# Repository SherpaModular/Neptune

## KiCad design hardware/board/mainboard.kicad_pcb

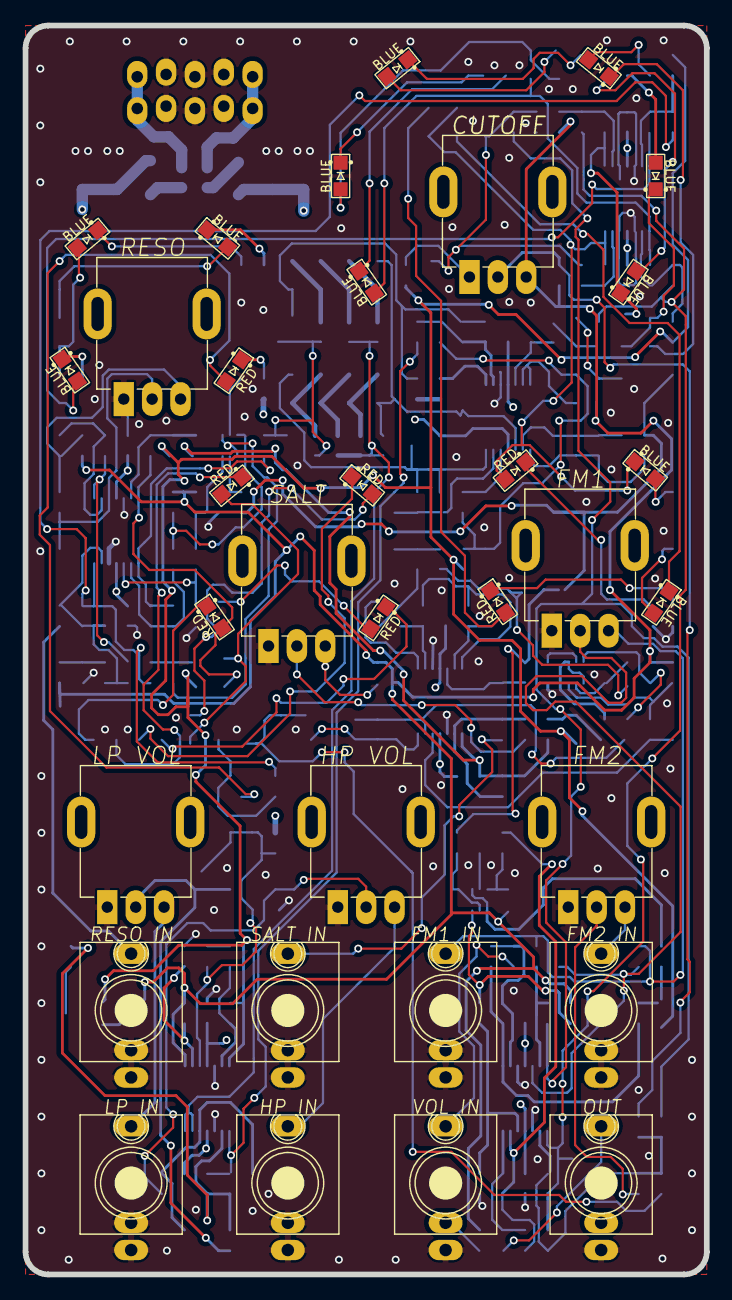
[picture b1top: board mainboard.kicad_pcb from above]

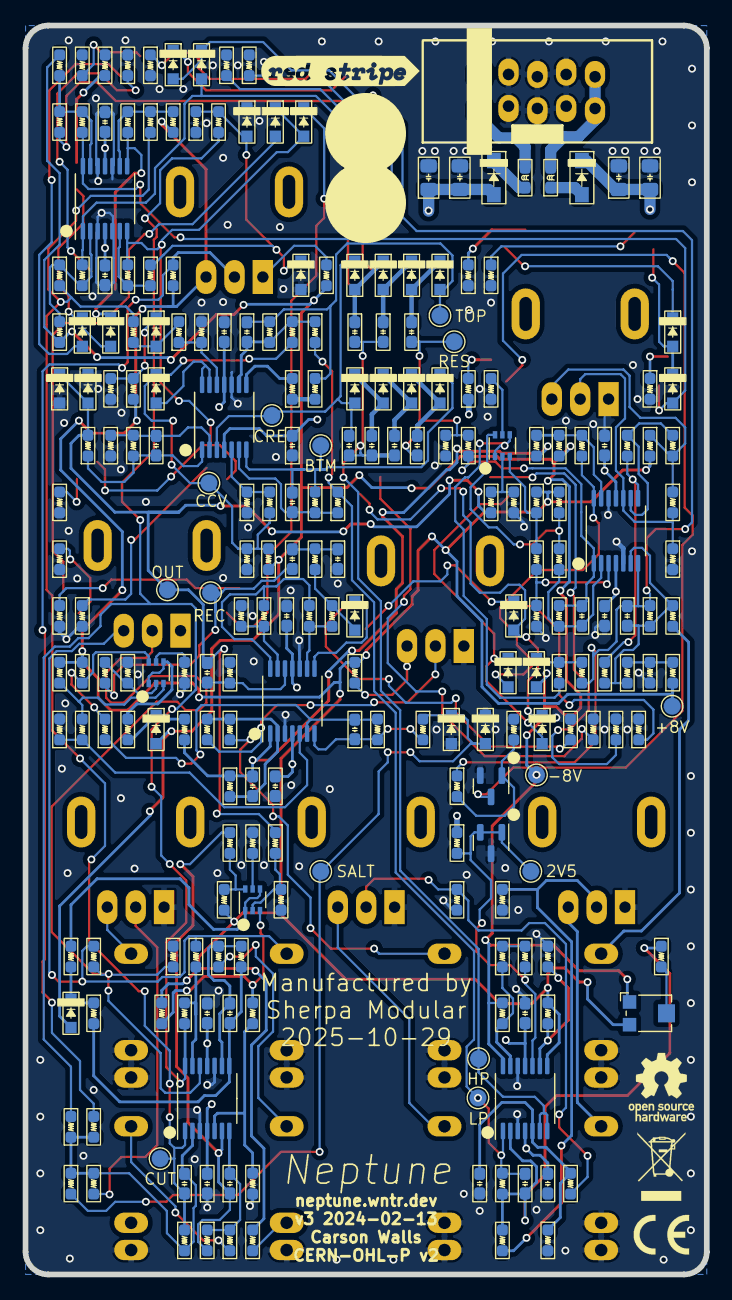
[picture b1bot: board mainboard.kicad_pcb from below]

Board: 4 copper layers, 60.0 x 110.0 mm, 273 parts (240 on the bottom side), 151 nets.

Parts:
C201, C202, C203, C204: 10u; C_0805_HandSolder
C206, C207, C208, C209, C210, C211, C212, C213, C214, C215, C216, C217: 100n; C_0603_HandSolder
C301, C302, C503, C504, C505, C506, C507, C508, C509: 1n; C_0603_HandSolder
C401, C501, C502, C510, C705: 100p; C_0603_HandSolder
C601, C702, C704, C801: 330p; C_0603_HandSolder
C602, C802: 10p; C_0603_HandSolder
C701, C703: 220n; C_0603_HandSolder
D201, D202: 30V; D_SOD-123+SOD-123F
D501, D502, D503, D504, D505, D506, D507, D508, D509, D510, D511, D512, D601, D701, D702, D703, D704, D801, D902, D904, D907, D909, D912, D914, D916, D919, D921, D927, D928, D929, D930: BAS315; D_SOD-323
D901, D903, D905, D906, D908, D910, D918, D920, D922, D925, D931: BLUE; LED_0805_Kingbright_APT2012
D911, D913, D915, D917, D924, D926, D932: RED; LED_0805_Kingbright_APT2012
FB201, FB202: 1k @ 100MHz; L_0603_HandSolder
J201: Power; Eurorack_Power_2x5_Shrouded_Lock_LongPads
J301, J302, J401, J402, J601, J701, J801, J802: AudioJack_WQP518MA_Compact_S_LongPads
Q601, Q701, Q801: BCM847; SOT-363_SC-70-6
Q901: MMBT3906; SOT-23
R201, R203, R303, R306, R515, R516, R519, R603, R604, R605, R612, R624, R704, R705, R713, R722, R804, R815, R904, R905, R906, R910, R911, R912, R916, R917, R918, R919, R923, R924, R925, R929, R930, R931, R932, R933, R935: 1k; R_0603_HandSolder
R202, R302, R305, R403, R404, R505, R606, R607, R609, R610, R611, R702, R710, R711, R712, R901, R907, R908: 100k; R_0603_HandSolder
R204, R405, R409, R518, R802, R803, R903, R909: 68k; R_0603_HandSolder
R205, R206, R307, R621, R622, R720, R721: 220k; R_0603_HandSolder
R301, R304, R501, R504, R602, R623, R709: 5k6; R_0603_HandSolder
R401, R410, R411, R517, R614, R619, R620, R718, R719: 3k9; R_0603_HandSolder
R402, R706, R707, R801, R915, R927: 39k; R_0603_HandSolder
R406, R407, R507, R913, R922: 33k; R_0603_HandSolder
R408, R601, R613, R701, R703, R714, R805, R806, R811, R812, R920: 10k; R_0603_HandSolder
R502, R926, R934, R936: 1k8; R_0603_HandSolder
R503, R608, R813, R814, R902, R914, R921, R928: 330k; R_0603_HandSolder
R506, R508, R509, R510, R511, R512, R513, R514, R617, R618, R716, R717, R809, R810: 20k; R_0603_HandSolder
R615, R616, R708, R715, R807, R808: 100R; R_0603_HandSolder
RV301, RV302, RV401, RV402, RV403, RV601, RV701: 10k; Potentiometer_Alpha_R0904N_LongPads
RV303: 10k; Potentiometer_Bourns_TC33X_Vertical
TP201, TP202, TP203, TP401, TP501, TP502, TP503, TP504, TP505, TP506, TP507, TP508, TP701, TP702: TestPoint_Pad_D1.5mm
U1, U2, U3, U4, U5, U6: TL074; TSSOP-14_4.4x5mm_P0.65mm
U201: TL431A; SOT-23

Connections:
+8VREF: R205.1, R402.1, R504.1, R601.1, R602.2, R617.2, R618.1, R709.2, R716.2, R717.1, R801.2, R809.2, R810.1, R908.2, RV303.3, RV401.3, TP202.1, U1.8
+12V: C201.1, C203.1, C206.2, C208.2, C210.2, C212.2, C214.2, C216.2, D201.1 (K), R201.1, U1.4 (V+), U2.4 (V+), U3.4 (V+), U4.4 (V+), U5.4 (V+), U6.4 (V+)
-8VREF: D601.2 (A), D702.2 (A), D801.2 (A), R206.1, R401.2, R506.2, R902.2, R914.2, R921.2, RV303.1, TP203.1, U1.14
-12V: C202.1, C204.1, C207.2, C209.2, C211.2, C213.2, C215.2, C217.2, D202.2 (A), R926.1, U1.11 (V-), U2.11 (V-), U3.11 (V-), U4.11 (V-), U5.11 (V-), U6.11 (V-)
/Cutoff CV Driver/CUTOFF_OUT: C401.1, R409.2, R501.2, R901.2, R907.2, TP401.1, U2.1
/Cutoff CV Driver/FM1_OUT: R404.1, R406.2, R933.1, U2.14
/Cutoff CV Driver/SALT_IN: D703.1 (K), D704.2 (A), R408.2, R722.1, TP702.1
/Filter Core/HIGH_PASS_IN: C504.2, C505.2, C506.2, C507.2, C508.2, TP504.1, U1.6 (-), U1.7
/Filter Core/LOW_PASS_IN: C301.1, R303.1, R509.2, R510.2, TP502.1, U1.1
/Filter Core/OUT: C701.2, D511.1 (K), D512.2 (A), R519.2, R614.2, R805.1, TP508.1
/Filter Core/RESONANCE_IN: C503.2, C509.2, R623.2, R624.1, TP503.1
/LED Drivers/RESONANCE_CV_IN: C601.1, R611.1, R612.2, R920.2, R935.1, U4.7
/LED Drivers/SALT_CV_IN: C704.1, R712.1, R713.2, R913.2, U5.1
/Power/2.5v unbuffered: R201.2, R203.1, TP201.1, U1.10 (+), U201.1 (K), U201.2 (REF)
/Resonance VCA/Resonance_CV: J601.T (Tip), R608.2
/Resonance VCA/Resonance_Offset: R601.2, R603.2, R609.2
/Resonance VCA/Resonance_Potentiometer: R607.1, R610.2, U4.8
GND: C201.2, C202.2, C203.2, C204.2, C206.1, C207.1, C208.1, C209.1, C210.1, C211.1, C212.1, C213.1, C214.1, C215.1, C216.1, C217.1, C302.2, C702.2, D511.2 (A), D512.1 (K), D703.2 (A), D704.1 (K), D929.1 (K), D930.2 (A), J201.3 (GND), J201.4 (GND), J201.5 (GND), J201.6 (GND), J201.7 (GND), J201.8 (GND), J301.S (Sleeve), J301.TN (Tip_normalize), J302.S (Sleeve), J302.TN (Tip_normalize), J401.S (Sleeve), J401.TN (Tip_normalize), J402.S (Sleeve), J402.TN (Tip_normalize), J601.S (Sleeve), J601.TN (Tip_normalize), J701.S (Sleeve), J701.TN (Tip_normalize), J801.S (Sleeve), J802.S (Sleeve), Q901.2 (E), R202.2, R301.2, R304.2, R306.2, R411.2, R502.2, R505.2, R507.1, R512.1, R517.1, R603.1, R605.2, R615.2, R616.1, R621.2, R624.2, R701.2, R702.1, R708.2, R715.1, R720.2, R807.2, R808.1, R813.2, R904.2, R905.2, R906.2, R910.2, R911.2, R912.2, R916.2, R917.2, R918.2, R919.2, R923.2, R924.2, R925.2, R929.1, R930.2, R931.1, R932.2, R934.1, R936.2, RV301.1, RV302.1, RV402.1, RV403.1, RV601.1, RV701.1, U1.3 (+), U1.12 (+), U2.3 (+), U2.10 (+), U3.10 (+), U4.5 (+), U4.12 (+), U5.3 (+), U5.10 (+), U6.3 (+), U6.5 (+), U6.10 (+), U6.12 (+), U201.3 (A)
unnamed: C510.1, R518.2, R519.1, U3.1
unnamed: C602.2, R622.1, R623.1, U4.1
unnamed: C702.1, C703.2, R706.1
unnamed: C703.1, R707.1, TP701.1
unnamed: C705.1, R721.1, R722.2, U5.7
unnamed: C801.1, R803.1, R804.2, U2.8
unnamed: C802.2, R814.1, R815.2, U2.7
unnamed: D201.2 (A), FB201.1
unnamed: D202.1 (K), FB202.1
unnamed: D501.2 (A), R501.1, R503.2
unnamed: D501.1 (K), R502.1, R504.2
unnamed: D502.2 (A), U3.13 (-), U3.14
unnamed: D502.1 (K), R506.1, R507.2, R508.2, R511.2, TP501.1
unnamed: C501.1, D503.2 (A), R513.1, R515.1, TP505.1
unnamed: C503.1, D503.1 (K), D504.2 (A)
unnamed: C504.1, D504.1 (K), D505.2 (A)
unnamed: C505.1, D505.1 (K), D506.2 (A)
unnamed: C506.1, D506.1 (K), D507.2 (A), TP507.1, U3.3 (+)
unnamed: C507.1, D507.1 (K), D508.2 (A)
unnamed: C508.1, D508.1 (K), D509.2 (A)
unnamed: C509.1, D509.1 (K), D510.2 (A)
unnamed: C502.1, D510.1 (K), R514.1, TP506.1, U3.7
unnamed: D601.1 (K), R612.1, R613.2
unnamed: D701.2 (A), R705.1, R706.2
unnamed: D701.1 (K), U5.8
unnamed: D702.1 (K), R713.1, R714.2
unnamed: D801.1 (K), R804.1, R806.2
unnamed: D901.2 (A), D902.2 (A), R903.2, U6.1
unnamed: D901.1 (K), R904.1
unnamed: D902.1 (K), D903.2 (A), D904.2 (A)
unnamed: D903.1 (K), R905.1
unnamed: D904.1 (K), D905.2 (A)
unnamed: D905.1 (K), R906.1
unnamed: D906.2 (A), R910.1
unnamed: D906.1 (K), D907.1 (K), R909.2, U6.8
unnamed: D907.2 (A), D908.1 (K), D909.1 (K)
unnamed: D908.2 (A), R911.1
unnamed: D909.2 (A), D910.1 (K)
unnamed: D910.2 (A), R912.1
unnamed: D911.2 (A), D912.2 (A), R915.2, U4.14
unnamed: D911.1 (K), R916.1
unnamed: D912.1 (K), D913.2 (A), D914.2 (A)
unnamed: D913.1 (K), R917.1
unnamed: D914.1 (K), D915.2 (A), D916.2 (A)
unnamed: D915.1 (K), R918.1
unnamed: D916.1 (K), D917.2 (A)
unnamed: D917.1 (K), R919.1
unnamed: D918.2 (A), D919.2 (A), R922.1, U6.14
unnamed: D918.1 (K), R923.1
unnamed: D919.1 (K), D920.2 (A), D921.2 (A)
unnamed: D920.1 (K), R924.1
unnamed: D921.1 (K), D922.2 (A)
unnamed: D922.1 (K), R925.1
unnamed: D924.2 (A), Q901.3 (C)
unnamed: D924.1 (K), R926.2
unnamed: D925.2 (A), R929.2
unnamed: D925.1 (K), D926.2 (A), D927.1 (K), D928.2 (A), R928.1, U6.7
unnamed: D926.1 (K), R930.1
unnamed: D927.2 (A), D931.1 (K)
unnamed: D928.1 (K), D932.2 (A)
unnamed: D929.2 (A), D930.1 (K), R927.1, R933.2, R934.2
unnamed: D931.2 (A), R931.2
unnamed: D932.1 (K), R932.1
unnamed: FB201.2, J201.9 (+12V), J201.10 (+12V)
unnamed: FB202.2, J201.1 (-12V), J201.2 (-12V)
unnamed: J301.T (Tip), RV301.3
unnamed: J302.T (Tip), RV302.3
unnamed: J401.T (Tip), R403.2, R410.1, RV402.3
unnamed: J402.T (Tip), RV403.3
unnamed: J701.T (Tip), R710.2
unnamed: J801.T (Tip), R802.2
unnamed: J801.TN (Tip_normalize), R801.1
unnamed: J802.T (Tip), R815.1
unnamed: Q601.2 (B), R614.1, R615.1
unnamed: Q601.5 (B), R616.2
unnamed: Q601.3 (C), R618.2, R620.2
unnamed: Q601.6 (C), R617.1, R619.2
unnamed: Q601.1 (E), Q601.4 (E), R613.1
unnamed: Q701.2 (B), R707.2, R708.1
unnamed: Q701.5 (B), R715.2
unnamed: Q701.3 (C), R717.2, R719.2
unnamed: Q701.6 (C), R716.1, R718.2
unnamed: Q701.1 (E), Q701.4 (E), R714.1
unnamed: Q801.2 (B), R805.2, R807.1
unnamed: Q801.5 (B), R808.2
unnamed: Q801.3 (C), R810.2, R812.2
unnamed: Q801.6 (C), R809.1, R811.2
unnamed: Q801.1 (E), Q801.4 (E), R806.1
unnamed: Q901.1 (B), R935.2, R936.1
unnamed: R203.2, R204.1
unnamed: R301.1, R302.2, RV301.2
unnamed: R304.1, R305.2, RV302.2
unnamed: R307.2, RV303.2
unnamed: R401.1, RV401.1
unnamed: R402.2, R405.1, RV401.2
unnamed: R407.2, RV403.2
unnamed: R515.2, R516.1
unnamed: R516.2, U3.8
unnamed: R602.1, R604.1, R606.2, RV601.3
unnamed: R703.1, R704.2, U5.14
unnamed: R709.1, RV701.3
unnamed: R711.2, RV701.2
unnamed: C301.2, R302.1, R303.2, R307.1, U1.2 (-)
unnamed: C302.1, R305.1, R306.1, U1.5 (+)
unnamed: R202.1, R205.2, U1.9 (-)
unnamed: R204.2, R206.2, U1.13 (-)
unnamed: C401.2, R405.2, R406.1, R407.1, R408.1, R409.1, U2.2 (-)
unnamed: R812.1, R813.1, U2.5 (+)
unnamed: C802.1, R811.1, R814.2, U2.6 (-)
unnamed: C801.2, R802.1, R803.2, U2.9 (-)
unnamed: R410.2, R411.1, RV402.2, U2.12 (+)
unnamed: R403.1, R404.2, U2.13 (-)
unnamed: C510.2, R517.2, R518.1, U3.2 (-)
unnamed: R511.1, R512.2, U3.5 (+)
unnamed: C502.2, R510.1, R514.2, U3.6 (-)
unnamed: C501.2, R508.1, R509.1, R513.2, U3.9 (-)
unnamed: R503.1, R505.1, U3.12 (+)
unnamed: R620.1, R621.1, U4.3 (+)
unnamed: C602.1, R619.1, R622.2, U4.2 (-)
unnamed: C601.2, R608.1, R609.1, R610.1, R611.2, U4.6 (-)
unnamed: R604.2, R605.1, RV601.2, U4.10 (+)
unnamed: R606.1, R607.2, U4.9 (-)
unnamed: R913.1, R914.1, R915.1, U4.13 (-)
unnamed: C704.2, R710.1, R711.1, R712.2, U5.2 (-)
unnamed: R719.1, R720.1, U5.5 (+)
unnamed: C705.2, R718.1, R721.2, U5.6 (-)
unnamed: R704.1, R705.2, U5.9 (-)
unnamed: C701.1, R702.2, U5.12 (+)
unnamed: R701.1, R703.2, U5.13 (-)
unnamed: R901.1, R902.1, R903.1, U6.2 (-)
unnamed: R927.2, R928.2, U6.6 (-)
unnamed: R907.1, R908.1, R909.1, U6.9 (-)
unnamed: R920.1, R921.1, R922.2, U6.13 (-)

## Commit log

2025-11-10 Remove logo; Add Sherpa Modular manufacturing note
2025-11-10 Remove white block from faceplate

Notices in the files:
hardware/board/mainboard.kicad_pcb:
CERN-OHL-P v2
